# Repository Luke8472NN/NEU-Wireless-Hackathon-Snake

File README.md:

# NEU-Wireless-Hackathon-Snake
Northeastern University Wireless Club 11/11/16 Hackathon Snake Game.

Copied from my old profile, https://github.com/Luke8472

Eternally grateful for https://github.com/devendrashivraj for the board design!

## Description
A Snake Game coded in Arduino and uploaded to an Arduino Uno. A PCB was designed as a shield for the Arduino Uno, and to house all electronic components.

## How it Works
1) Turn the game on, using the power switch located in the upper left corner of the PCB.
2) Press the joystick once, to start playing the game.
3) The direction of the snake can be controlled using the joystick.
4) The speed of the snake can be controlled using the potentiometer located to the left of the joystick.
5) The option for walls on or off can be controlled by the switch below the potentiometer. </br>
   a) If the walls are on, the user loses if the snake hits the edge of the display. </br>
   b) If the walls are off, the snake can go out one edge, and come in through the other (world wraps around).
6) The score is displayed above the joystick, and represents the number of candies eaten by the snake.
7) If the game is left idle for more than 15 seconds, a Snake AI will begin playing the game.

## Goal of the Game
Eat all of the candy without having the snake cross over itself. Once the snake grows to the size of the display (score = 128), the user wins.

## Prerequisites
LedControl library: https://github.com/wayoda/LedControl

## Board Design

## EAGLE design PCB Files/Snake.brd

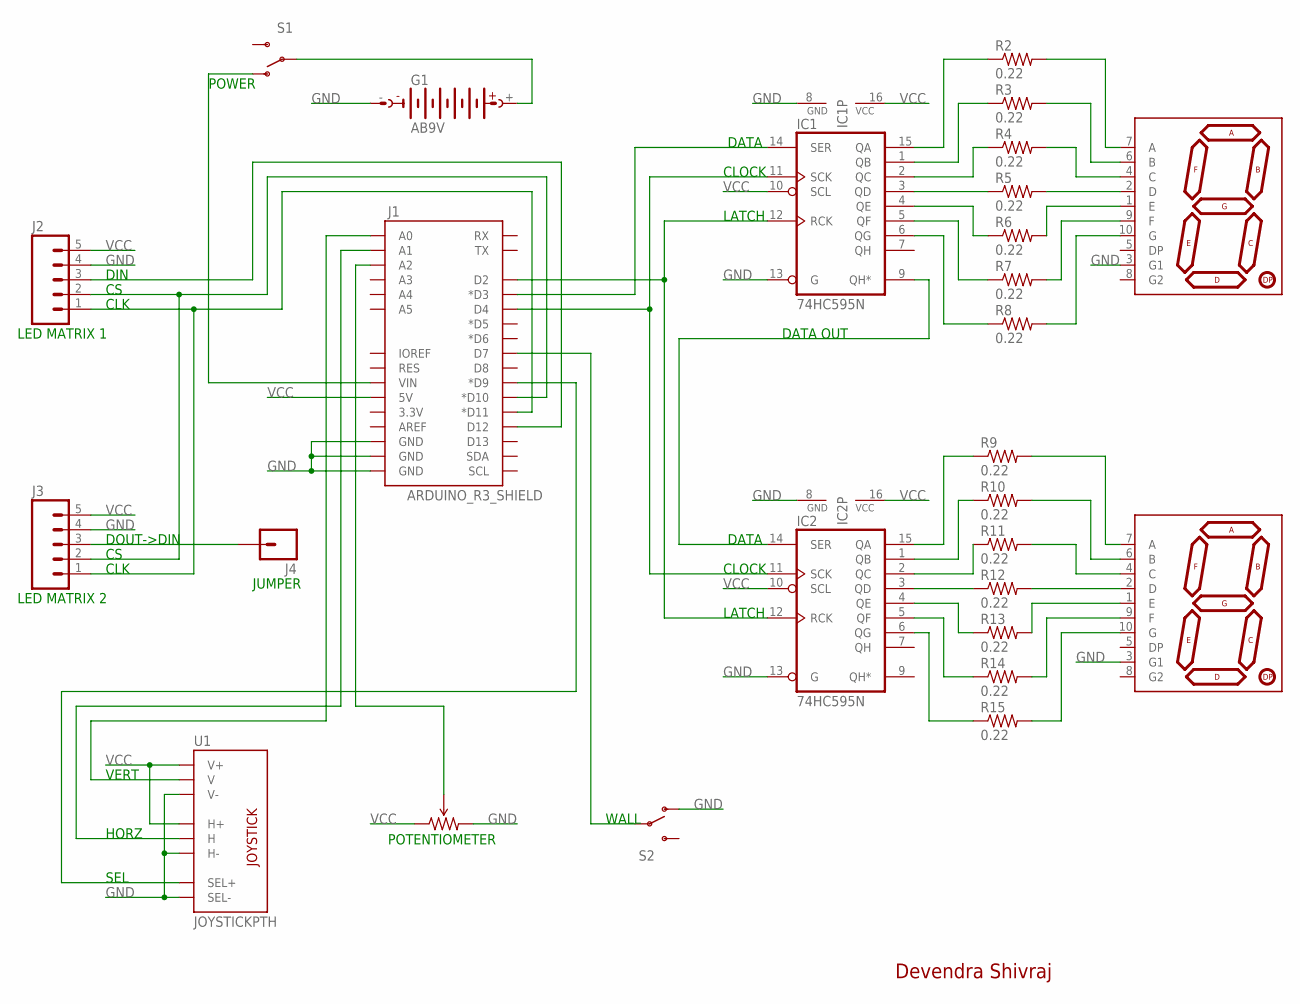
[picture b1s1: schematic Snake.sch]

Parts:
G1: AB9V
IC1, IC2: 74HC595N; DIL16
J1: ARDUINO_R3_SHIELD; UNO_R3_SHIELD
J2, J3: M05PTH; 1X05
J4: M01PTH; 1X01
R1: TSR-3386; 3386U
R2, R3, R4, R5, R6, R7, R8, R9, R10, R11, R12, R13, R14, R15: 0.22; 0805
S1, S2: SWITCH-SPDTPTH; SWITCH-SPDT
U1: JOYSTICKPTH; JOYSTICK
U$1, U$2: 7-SEGMENT-DISPLAYPTH; 7-SEGMENT-DISPLAY

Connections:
+: G1.+, S1.2
A2: J1.A2, R1.2 (WIPER)
CLK: J1.D11 (*D11), J2.1, J3.1
CLOCK: IC1.11 (SCK), IC2.11 (SCK), J1.D4
CS: J1.D10 (*D10), J2.2, J3.2
DATA: IC1.14 (SER), J1.D3 (*D3)
DATA_SHIFT: IC1.9 (QH*), IC2.14 (SER)
DIN: J1.D12, J2.3
GND: G1.-, IC1.8 (GND), IC1.13 (G), IC2.8 (GND), IC2.13 (G), J1.GND@0 (GND), J1.GND@1 (GND), J1.GND@2 (GND), J2.4, J3.4, R1.3 (CW), S2.1 (O), U1.B2A (SEL-), U1.H3 (H-), U1.V3 (V-), U$1.3 (G1), U$2.3 (G1)
HORZ: J1.A1, U1.H2 (H)
LATCH: IC1.12 (RCK), IC2.12 (RCK), J1.D2
unnamed: J3.3, J4.1
unnamed: J1.VIN, S1.1 (O)
unnamed: IC1.15 (QA), R2.1
unnamed: IC1.1 (QB), R3.1
unnamed: IC1.2 (QC), R4.1
unnamed: IC1.3 (QD), R5.1
unnamed: IC1.4 (QE), R6.1
unnamed: IC1.5 (QF), R7.1
unnamed: IC1.6 (QG), R8.1
unnamed: R2.2, U$1.7 (A)
unnamed: R3.2, U$1.6 (B)
unnamed: R4.2, U$1.4 (C)
unnamed: R5.2, U$1.2 (D)
unnamed: R6.2, U$1.1 (E)
unnamed: R7.2, U$1.9 (F)
unnamed: R8.2, U$1.10 (G)
unnamed: IC2.15 (QA), R9.1
unnamed: J1.D7, S2.2
unnamed: IC2.1 (QB), R10.1
unnamed: IC2.2 (QC), R11.1
unnamed: IC2.3 (QD), R12.1
unnamed: IC2.4 (QE), R13.1
unnamed: IC2.5 (QF), R14.1
unnamed: IC2.6 (QG), R15.1
unnamed: R9.2, U$2.7 (A)
unnamed: R10.2, U$2.6 (B)
unnamed: R11.2, U$2.4 (C)
unnamed: R12.2, U$2.2 (D)
unnamed: R13.2, U$2.1 (E)
unnamed: R14.2, U$2.9 (F)
unnamed: R15.2, U$2.10 (G)
SEL: J1.D9 (*D9), U1.B1A (SEL+)
VCC: IC1.10 (SCL), IC1.16 (VCC), IC2.10 (SCL), IC2.16 (VCC), J1.5V, J2.5, J3.5, R1.1 (CCW), U1.H1 (H+), U1.V1 (V+)
VERT: J1.A0, U1.V2 (V)

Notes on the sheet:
DATA
CLOCK
LATCH
DATA OUT
VERT
HORZ
SEL
WALL
DIN
CLK
POWER
LED MATRIX 1
LED MATRIX 2
POTENTIOMETER
JUMPER
DOUT->DIN
Devendra Shivraj

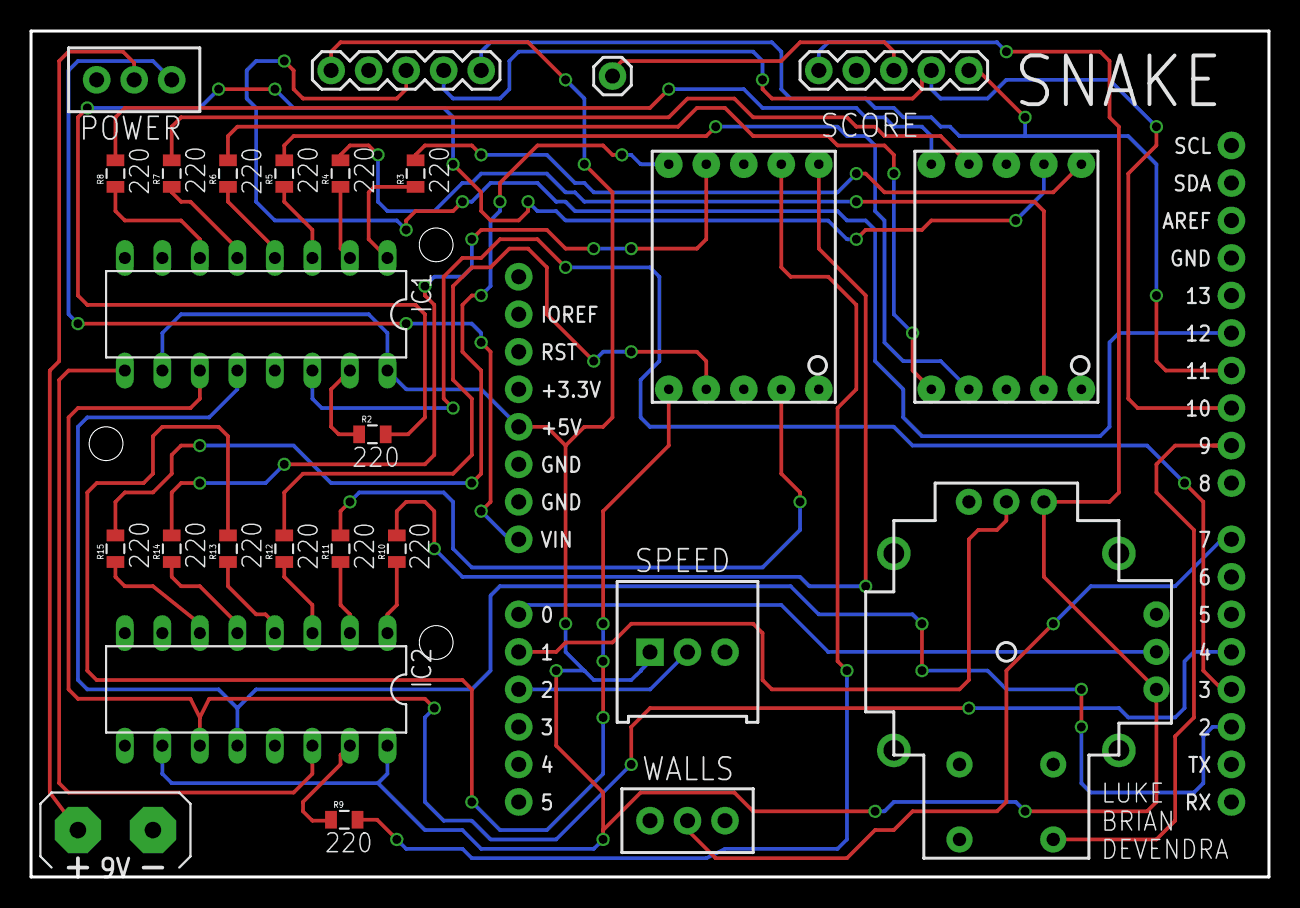
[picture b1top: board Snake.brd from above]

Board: 2 copper layers, 83.8 x 57.3 mm, 27 parts (0 on the bottom side), 45 nets.

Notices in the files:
parts and their libraries:
SparkFun-Boards: Licensing: Creative Commons ShareAlike 4.0 International - https://creativecommons.org/licenses/by-sa/4.0
